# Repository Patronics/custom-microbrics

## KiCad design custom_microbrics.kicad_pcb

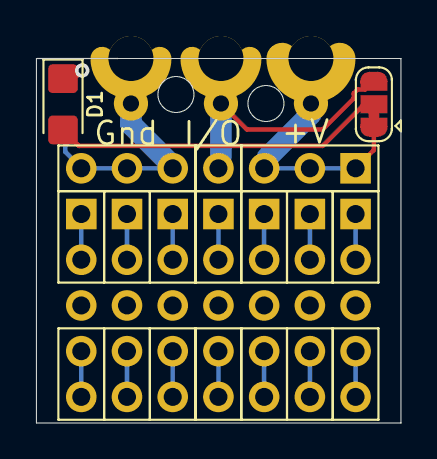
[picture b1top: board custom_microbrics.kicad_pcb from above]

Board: 2 copper layers, 20.2 x 20.2 mm, 12 parts (1 on the bottom side), 19 nets.

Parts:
D1: LED; LED_1206_3216Metric_Castellated
J1, J2, J3, J4, J5, J7, J8: Conn_01x05; PinHeader_1x05_P2.54mm_Vertical_BreadBoardySilkScreen
J6: Conn_01x07; PinHeader_1x07_P2.54mm_Vertical
JP1: SolderJumper_3_Bridged12; SolderJumper-3_P1.3mm_Bridged12_RoundedPad1.0x1.5mm
MB1: MicroBric; microbric
R1: R_Small; R_1206_3216Metric_Pad1.30x1.75mm_HandSolder

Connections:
unnamed: D1.1, R1.2
unnamed: D1.2, JP1.2
unnamed: J1.1, J1.2
unnamed: J1.4, J1.5
unnamed: J2.1, J2.2
unnamed: J2.4, J2.5
unnamed: J3.1, J3.2
unnamed: J3.4, J3.5
unnamed: J4.1, J4.2
unnamed: J4.4, J4.5
unnamed: J5.1, J5.2
unnamed: J5.4, J5.5
unnamed: J6.1, J6.2, J6.3, JP1.1, MB1.3
unnamed: J6.4, JP1.3, MB1.2
unnamed: J6.5, J6.6, J6.7, MB1.1, R1.1
unnamed: J7.1, J7.2
unnamed: J7.4, J7.5
unnamed: J8.1, J8.2
unnamed: J8.4, J8.5

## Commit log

2021-01-20 initial project
2021-01-20 add initial symbol for microbric connector
2021-01-20 intitial microbric pad and hole layout attempt
2021-01-20 finished schematic layout and added pcb layout
2021-01-22 added lables for +v, Gnd, and I/O
2021-01-23 switched traces to bottom layer to allow single-sided machining
2021-01-23 widen tracks to simplifiy machining and increase current capacity (will likely want to reduce again for higher complexity boards)
2021-01-27 Starting Scad file for connector brick
2021-01-27 added holes to connector brick
2021-01-29 tweaks for printability and manufacturability
2021-02-03 larger holes in the footprint
2021-02-03 schematic and pcb for psuedo breadboard
2021-02-03 led module
2021-02-19 minor tweaks
2021-02-19 initial design of stripboard2 layout, rotated rows/columns, and added optional smt LED (with jumper to configure between power or gpio-tied output)
2021-02-24 added silkscreen layer to match electrical connections
2021-02-24 switch unneeded silkscreen to dwgs.user
2021-02-24 fix accidentally overwritten file in previous commit
